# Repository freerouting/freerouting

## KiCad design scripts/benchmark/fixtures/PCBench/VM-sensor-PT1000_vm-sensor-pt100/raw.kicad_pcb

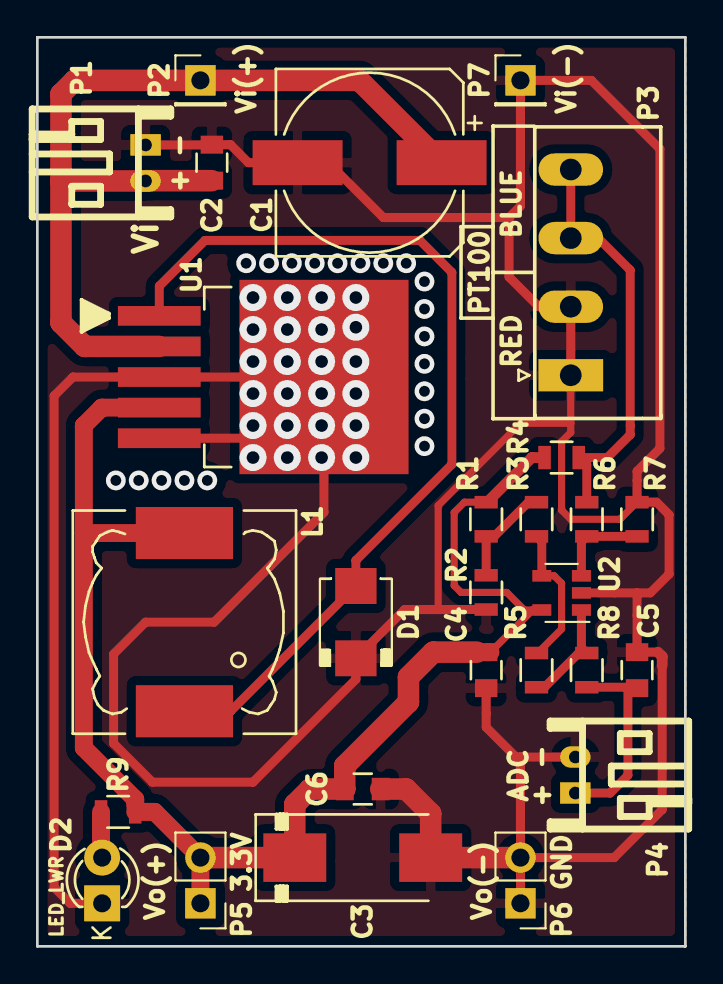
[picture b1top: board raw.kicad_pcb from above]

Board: 2 copper layers, 36.0 x 50.5 mm, 27 parts (0 on the bottom side), 11 nets.

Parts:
C1: 470uF/50v; c_elec_10x10.5
C2, C6: 10uF/16v; C_0805
C3: 330uF/16V; Tantalum_Case-D_EIA-7343-31_Hand
C4, C5: 10uF; C_0805
D1: SS34; do214aa-g
D2: LED_Small; LED-3MM
L1: 47uH/RH127-470; Choke_SMD_12x12mm_h8mm
P1: Vi; s2b-ph-kl
P2: Vin(+); Pin_Header_Straight_1x01_Pitch2.54mm
P3: PT100; Domino-PT100.pretty
P4: ADC; s2b-ph-kl
P5: Vo(+); Pin_Header_Straight_1x02_Pitch2.54mm
P6: Vo(-); Pin_Header_Straight_1x02_Pitch2.54mm
P7: Vin(-); Pin_Header_Straight_1x01_Pitch2.54mm
R1, R4: 3.3K/1%; R_0805
R2: 100R/1%; R_0805
R3, R6: 16.9K/1%; R_0805
R5, R7: 1M/1%; R_0805
R8: 1K/1%; R_0805
R9: 100R; R_0805
U1: LM2595S-3.3; TO-263-5Lead
U2: MCP601T; SOT-23-5

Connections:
+3V3: C3.1, C4.1, C6.1, L1.2, P5.1, P5.2, R1.1, R4.1, R9.1, U1.4, U2.5
/ADC: C5.1, P4.1, R8.1
/Blue: P3.3, P3.4, R4.2, R6.2
GND: C1.2, C2.2, C3.2, C4.2, C5.2, C6.2, D1.2, D2.1, P1.1, P3.1, P3.2, P4.2, P6.1, P6.2, P7.1, R2.2, R7.1, U1.3, U1.5, U2.2
unnamed: D1.1, L1.1, U1.1
unnamed: D2.2, R9.2
unnamed: R1.2, R2.1, R3.2
unnamed: R3.1, R5.1, U2.4
unnamed: R5.2, R8.2, U2.1
unnamed: R6.1, R7.2, U2.3
VCC: C1.1, C2.1, P1.2, P2.1, U1.2

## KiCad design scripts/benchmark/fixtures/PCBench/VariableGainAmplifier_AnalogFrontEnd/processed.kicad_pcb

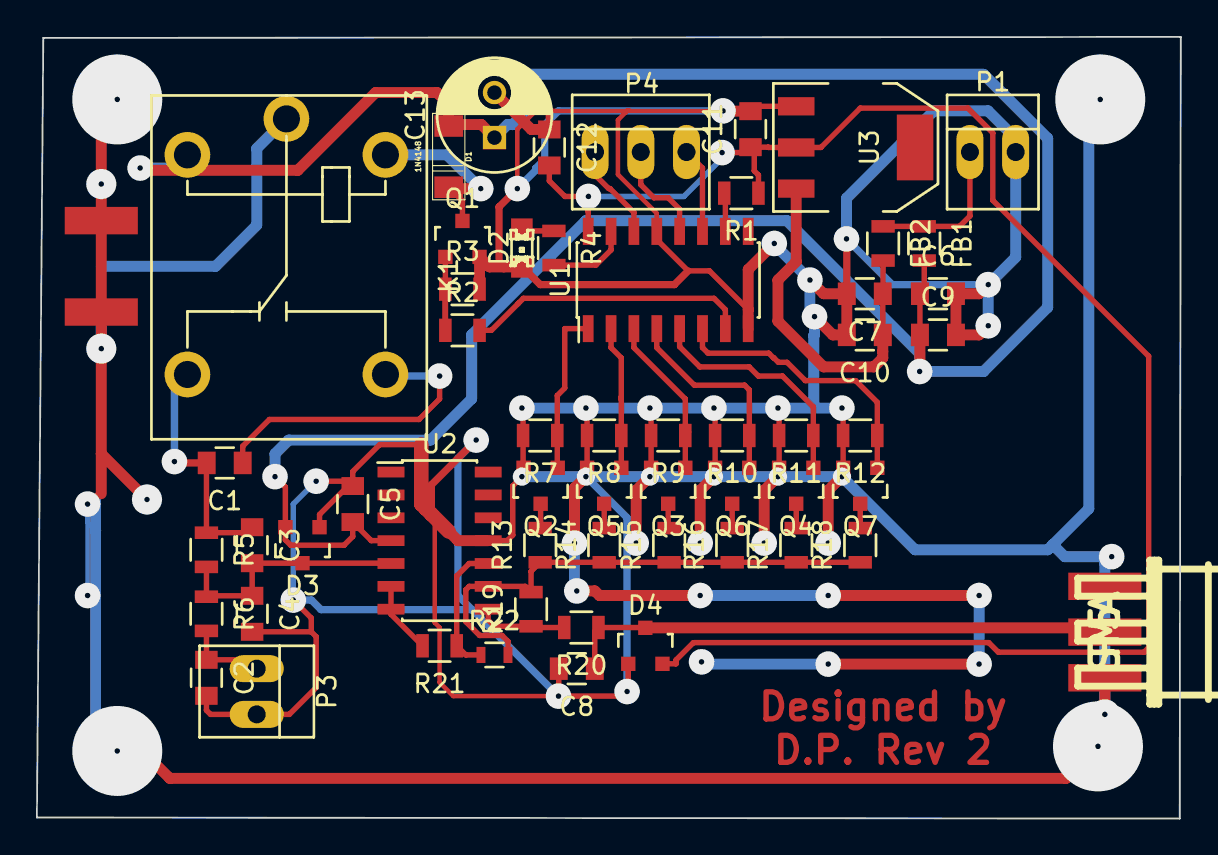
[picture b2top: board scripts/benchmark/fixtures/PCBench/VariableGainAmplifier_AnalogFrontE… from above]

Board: 2 copper layers, 63.5 x 43.4 mm, 57 parts (1 on the bottom side), 36 nets.

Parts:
C1, C2, C5, C6, C7, C12: 100n; C_0805
C3: 12pF; C_0805
C4: 47pF; C_0805
C8: 10p; C_0805
C9, C10, C11: 10u; C_0805
C13: 100u; C_Radial_D6.3_L11.2_P2.5
D1: 1N4148; MiniMelf
D2: LED; LED-0805
D3, D4: BAT54S; SOT-23
FB1, FB2: MH2029-300Y; Ind_0805
K1: RELAY_SONGLE_RD-XVDC-SL-C; SONGLE_SRD-XVDC-SL-C
P1: Power; PINHEAD1-2
P2, P5: SMA; CON-SMA-EDGE
P3: DAC_Offset; PINHEAD1-2
P4: ShiftReg; PINHEAD1-3
Q1: MMBT2222A; SOT-23
Q2, Q3, Q4, Q5, Q6, Q7: Si2302DS; SOT-23
R1, R3, R7, R8, R9, R10, R11, R12: 10k; R_0805
R2: 1k; R_0805
R4: 330; R_0805
R5: 840k/1%; R_0805
R6: 160k/1%; R_0805
R13, R19: 200/1%; R_0805
R14: 1M/1%; R_0805
R15: 50; R_0805
R16, R20: 22; R_0805
R17: 10; R_0805
R18: 5; R_0805
R21: 0; R_0805
R22: 100; R_0603
U1: 74HC595; SOIC-16_3.9x9.9mm_Pitch1.27mm
U2: MCP660; SOIC-14_3.9x8.7mm_Pitch1.27mm
U3: LD1117S33TR; SOT-223

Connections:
/5V: C5.2, C6.1, C9.1, C13.1, D1.1, D3.2, FB1.2, K1.1, U2.4
/5V_IN: FB1.1, FB2.1, P1.1
/AC/DC: R2.2, U1.7
/DAC_Offset: C2.1, P3.1, R6.2
/SR_RCLK: P4.2, U1.12
/SR_SER: P4.1, U1.14
/SR_SRCLK: P4.3, U1.11
/V_IN: C8.1, D4.3, P5.1, R20.1
GND: C2.2, C4.2, C5.1, C6.2, C7.2, C8.2, C9.2, C10.2, C11.2, C12.1, C13.2, D2.1, D3.1, D4.1, P1.2, P2.2, P3.2, P5.2, Q1.2, Q2.2, Q3.2, Q4.2, Q5.2, Q6.2, Q7.2, R3.2, R7.2, R8.2, R9.2, R10.2, R11.2, R12.2, U1.8, U1.13, U2.11, U3.1
unnamed: C1.1, K1.5
unnamed: C1.2, C3.1, K1.4, R5.1
unnamed: C3.2, C4.1, D3.3, R5.2, R6.1, U2.5
unnamed: C7.1, C10.1, FB2.2, U3.3
unnamed: D1.2, K1.2, Q1.3
unnamed: D2.2, R4.1
unnamed: K1.3, P2.1
unnamed: Q1.1, R2.1, R3.1
unnamed: Q2.1, R7.1, U1.1
unnamed: Q2.3, R13.2
unnamed: Q3.1, R9.1, U1.3
unnamed: Q3.3, R15.2
unnamed: Q4.1, R11.1, U1.5
unnamed: Q4.3, R17.2
unnamed: Q5.1, R8.1, U1.2
unnamed: Q5.3, R14.2
unnamed: Q6.1, R10.1, U1.4
unnamed: Q6.3, R16.2
unnamed: Q7.1, R12.1, U1.6
unnamed: Q7.3, R18.2
unnamed: R1.2, U1.10
unnamed: R4.2, U1.15
unnamed: R13.1, R14.1, R15.1, R16.1, R17.1, R18.1, R19.2, R22.2, U2.9
unnamed: R19.1, R20.2, U2.8
unnamed: R21.1, R22.1, U2.10
unnamed: R21.2, U2.6, U2.7
VCC: C11.1, C12.2, D4.2, R1.1, U1.16, U3.2

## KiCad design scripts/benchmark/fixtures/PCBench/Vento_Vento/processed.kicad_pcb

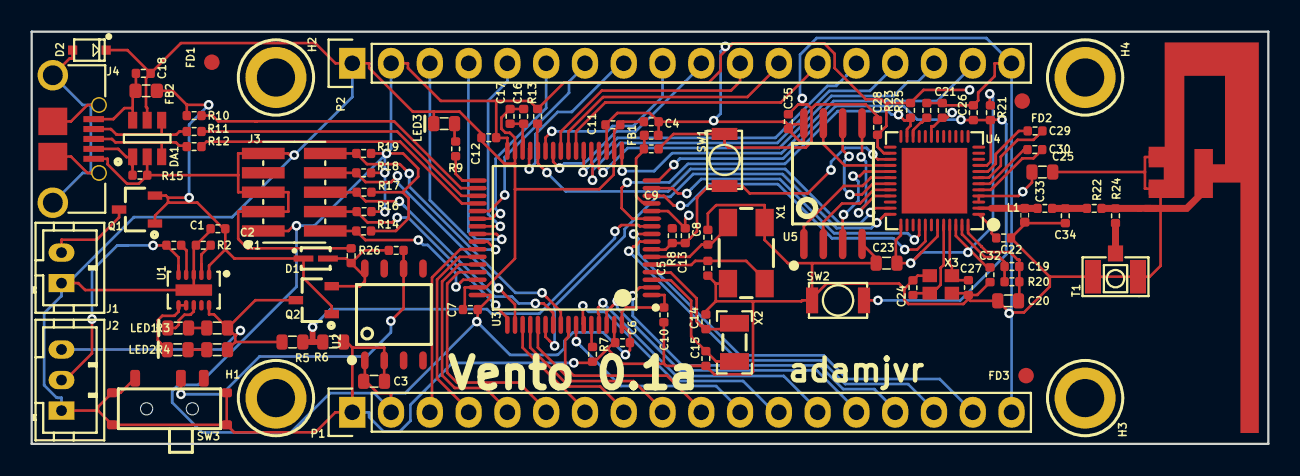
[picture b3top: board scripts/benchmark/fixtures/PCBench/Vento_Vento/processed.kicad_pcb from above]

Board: 4 copper layers, 81.0 x 27.0 mm, 97 parts (0 on the bottom side), 93 nets.

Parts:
ANT1: Inverted_F_PCB_Antenna; PCB_IF_ANT_2.4G
C1, C2: CL05A105KA5NQNC; C0402
C3, C23, C25: CL10A106KQ8NNNC; C0603
C4, C6, C7, C9, C10, C11, C12, C13, C17, C18, C21, C22, C26, C28, C32, C35: CL05B104JP5NNNC; C0402
C5, C8, C24, C27: CL05C090CB5NNNC; C0402
C14, C15: CL05C180GB5NCNC; C0402
C16: CL05A475KQ5NRNC; C0402
C19: GRM1557U1A302JA01D; C0402
C20: C0603C103J5JAC7867; C0603
C29, C30: GRM1555C1H271FA01D; C0402
C33: 600L3R9BT200T; C0402
C34: 600L2R4BT200T; C0402
D1: BAT20JFILM
D2: RSB39VTE-17
DA1: ESDA6V1BC6
FB1: BLM15HG601SN1D
FB2: MI0603K300R-10
FD1, FD2, FD3: FIDUCIAL
H1, H2, H3, H4: M2.5_Hole; M2.5_HOLE
J1: B2B-PH-K-S(LF)(SN)
J2: B3B-PH-K-S(LF)(SN)
J3: 20021121-00010C4LF
J4: 0475890001-MicroUSBPort; 0475890001
L1: 744901027; BLM15HG601SN1D
LED1: LTST-C191KGKT; LED0603
LED2: LTST-C191KFKT; LED0603
LED3: LTST-C193TBKT-5A; LED0603
P1, P2: CONN_01X18; Socket_Strip_Straight_1x18
Q1, Q2: DMG2307L-7
R1: RC1005F4870CS; R0402
R2, R8, R9, R14, R16, R17, R18, R19: RC1005F102CS; R0402
R3, R4: RC1608J202CS; R0603
R5, R6: ERA-3AEB3741V; R0603
R7, R10, R13, R21, R23, R25, R26: RC1005F103CS; R0402
R11, R12: CPF0402B22RE1; R0402
R15: RC1005J473CS; R0402
R20: RC1005F203CS; R0402
R22, R24: ERJ-2GE0R00X; R0402
SW1, SW2: B3U-1000P
SW3: CUS-12TB
T1: 1909763-1
U1: BQ24210DQCT; BQ24210
U2: TC1265-3.3VOA
U3: STM32F446RET6_-_TQFP64; STM32F446RET6
U4: ESP32
U5: W25Q64FWSSIG
X1: ABM3B8.000MHZB2T
X2: ABS07-32.768KHZ-9-T
X3: FA-128_26.0000MF10Z-AC3

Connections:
+3V3: C3.1, C4.1, C6.1, C7.1, C10.1, C11.1, C12.1, C21.1, C22.1, C23.1, C25.1, C28.1, C32.1, C35.1, FB1.1, J3.1, P1.2, P2.2, R13.1, R14.1, R16.1, R17.1, R18.1, R19.1, R21.1, R23.1, U2.1, U3.1, U3.19, U3.32, U3.48, U3.64, U4.1, U4.3, U4.4, U4.19, U4.26, U4.37, U4.43, U4.46, U5.8
/MCU_STM32F446RET6/BAT_VOLT: R5.2, R6.1, U3.10
/MCU_STM32F446RET6/ESPTOST_BOOT0: U3.54, U4.36
/MCU_STM32F446RET6/ESPTOST_BOOT1: R13.2, U3.28, U4.35
/MCU_STM32F446RET6/ESP_PGM_MODE: R23.2, U3.11, U4.23
/MCU_STM32F446RET6/ESP_ST_RST: C13.1, R8.2, SW1.1, U3.7, U4.27
/MCU_STM32F446RET6/ESP_URX: U3.14, U4.41
/MCU_STM32F446RET6/ESP_UTX: U3.15, U4.40
/MCU_STM32F446RET6/HEARTBEAT: R9.1, U3.33
/MCU_STM32F446RET6/NJTRST: J3.10, R19.2, U3.56
/MCU_STM32F446RET6/PA3: P2.17, U3.17
/MCU_STM32F446RET6/PA4: P2.16, U3.20
/MCU_STM32F446RET6/PA5: P2.15, U3.21
/MCU_STM32F446RET6/PA6: P2.14, U3.22
/MCU_STM32F446RET6/PA7: P2.13, U3.23
/MCU_STM32F446RET6/PA8: P2.3, U3.41
/MCU_STM32F446RET6/PA9: P1.3, U3.42
/MCU_STM32F446RET6/PA10: P1.4, U3.43
/MCU_STM32F446RET6/PA11: P1.5, U3.44
/MCU_STM32F446RET6/PA12: P1.6, U3.45
/MCU_STM32F446RET6/PB0: P2.10, U3.26
/MCU_STM32F446RET6/PB1: P2.9, U3.27
/MCU_STM32F446RET6/PB5: P1.10, U3.57
/MCU_STM32F446RET6/PB6: P1.11, U3.58
/MCU_STM32F446RET6/PB7: P1.12, U3.59
/MCU_STM32F446RET6/PB8: P1.13, U3.61
/MCU_STM32F446RET6/PB9: P1.14, U3.62
/MCU_STM32F446RET6/PB10: P2.8, U3.29
/MCU_STM32F446RET6/PC0: P1.16, U3.8
/MCU_STM32F446RET6/PC1: P1.17, U3.9
/MCU_STM32F446RET6/PC4: P2.12, U3.24
/MCU_STM32F446RET6/PC5: P2.11, U3.25
/MCU_STM32F446RET6/PC6: P2.7, U3.37
/MCU_STM32F446RET6/PC7: P2.6, U3.38
/MCU_STM32F446RET6/PC8: P2.5, U3.39
/MCU_STM32F446RET6/PC9: P2.4, U3.40
/MCU_STM32F446RET6/PC10: P1.7, U3.51
/MCU_STM32F446RET6/PC11: P1.8, U3.52
/MCU_STM32F446RET6/PC12: P1.9, U3.53
/MCU_STM32F446RET6/PC13: P1.15, U3.2
/MCU_STM32F446RET6/STM_ESP_RST: C26.1, R21.2, SW2.2, U3.16, U4.9
/MCU_STM32F446RET6/SWCLK_TCK: J3.4, R16.2, U3.49
/MCU_STM32F446RET6/SWDIO_TMS: J3.2, R14.2, U3.46
/MCU_STM32F446RET6/SWO_TDI: J3.8, R18.2, U3.50
/MCU_STM32F446RET6/SWO_TDO: J3.6, R17.2, U3.55
/MCU_STM32F446RET6/VBUS: C1.1, D1.1, FB2.1, Q1.1, Q1.2, Q2.1, R10.2, U1.1
/Power/BAT: J2.3, Q2.3, R3.2, R4.2, R5.1, U1.10
/Power/LDO_VIN: C2.1, D1.2, Q2.2, R26.1, U2.8
/Power/THERM: J2.2, R2.2, U1.5
/WiFi_BLE_ESP32/ANT: C33.2, C34.1, R22.1
/WiFi_BLE_ESP32/ANT_IF: ANT1.1, R22.2, R24.1
/WiFi_BLE_ESP32/ANT_UM: R24.2, T1.1
/WiFi_BLE_ESP32/CLK: U4.31, U5.6
/WiFi_BLE_ESP32/CS: U4.30, U5.1
/WiFi_BLE_ESP32/LNA: C33.1, L1.1, U4.2
/WiFi_BLE_ESP32/SD1: U4.33, U5.5
/WiFi_BLE_ESP32/SD2: U4.28, U5.7
/WiFi_BLE_ESP32/SD3: U4.29, U5.3
/WiFi_BLE_ESP32/SDO: U4.32, U5.2
GND: ANT1.2, C1.2, C2.2, C3.2, C4.2, C5.2, C6.2, C7.2, C8.2, C9.2, C10.2, C11.2, C12.2, C13.2, C14.2, C15.2, C16.2, C17.2, C18.1, C20.2, C21.2, C22.2, C23.2, C24.2, C25.2, C26.2, C27.2, C28.2, C32.2, C34.2, C35.2, D2.2, DA1.2, DA1.5, J1.1, J2.1, J3.3, J3.5, J3.9, J4.5, L1.2, LED3.2, P1.1, P1.18, P2.1, P2.18, R1.2, R6.2, R7.2, R15.2, R25.1, SW1.2, SW2.1, SW3.1, SW3.4, T1.2, U1.3, U1.11, U2.2, U3.12, U3.18, U3.31, U3.47, U3.63, U5.4, X1.2, X1.4, X3.2, X3.4
unnamed: C5.1, U3.5, X1.1
unnamed: C8.1, U3.6, X1.3
unnamed: C9.1, FB1.2, U3.13
unnamed: C14.1, U3.4, X2.1
unnamed: C15.1, U3.3, X2.2
unnamed: C16.1, C17.1, U3.30
unnamed: C18.2, DA1.6, FB2.2, J4.1
unnamed: C19.1, R20.1, U4.47
unnamed: C19.2, C20.1, R20.2, U4.48
unnamed: C24.1, U4.44, X3.1
unnamed: C27.1, U4.45, X3.3
unnamed: C29.1, U4.7
unnamed: C29.2, U4.8
unnamed: C30.1, U4.5
unnamed: C30.2, U4.6
unnamed: D2.1, J4.6, J4.7, J4.8, J4.9, J4.10, J4.11
unnamed: DA1.1, J4.4, R15.1
unnamed: DA1.3, J4.3, R12.2
unnamed: DA1.4, J4.2, R11.2
unnamed: J1.2, Q1.3
unnamed: LED1.1, R3.1
unnamed: LED1.2, U1.8
unnamed: LED2.1, R4.1
unnamed: LED2.2, U1.6, U1.7
unnamed: LED3.1, R9.2
unnamed: R1.1, U1.2
unnamed: R2.1, U1.4
unnamed: R7.1, U3.60
unnamed: R10.1, U3.34
unnamed: R11.1, U3.35
unnamed: R12.1, U3.36
unnamed: R25.2, U4.22
unnamed: R26.2, SW3.2, U2.6
